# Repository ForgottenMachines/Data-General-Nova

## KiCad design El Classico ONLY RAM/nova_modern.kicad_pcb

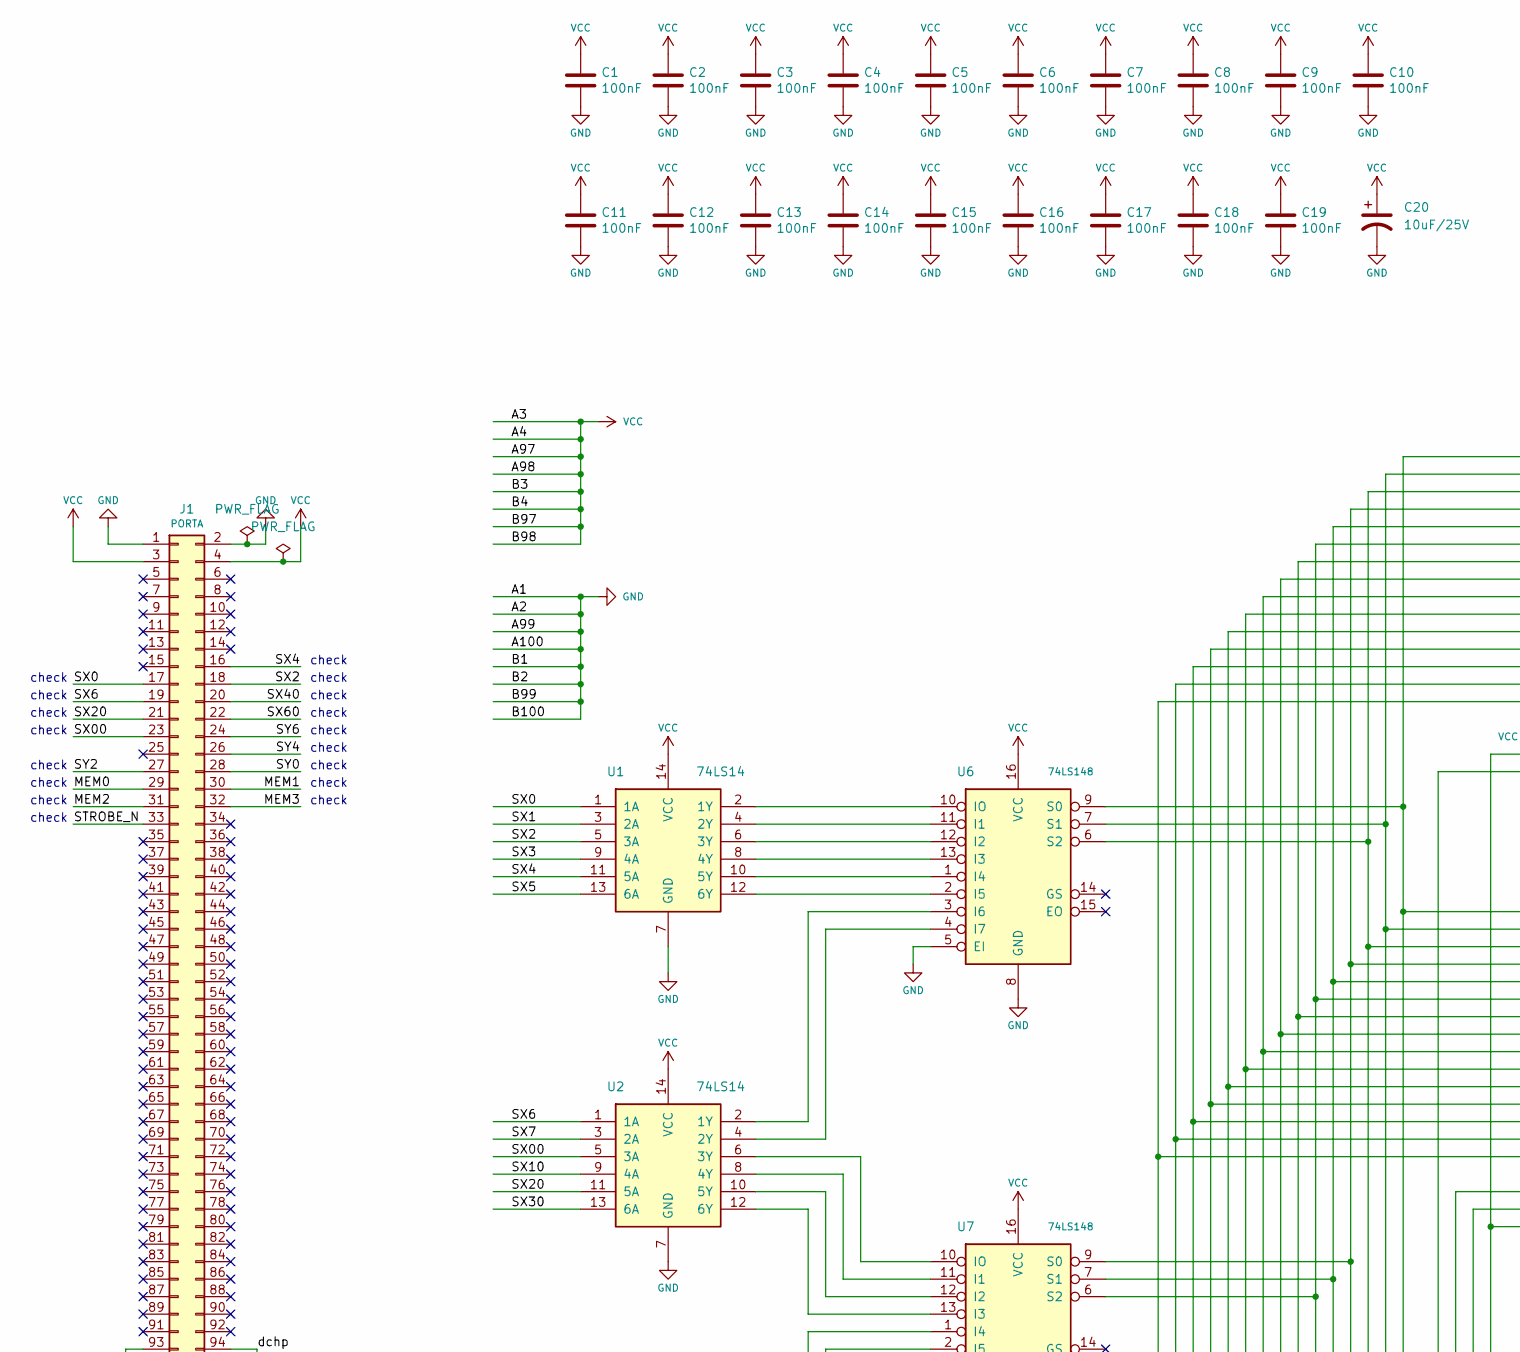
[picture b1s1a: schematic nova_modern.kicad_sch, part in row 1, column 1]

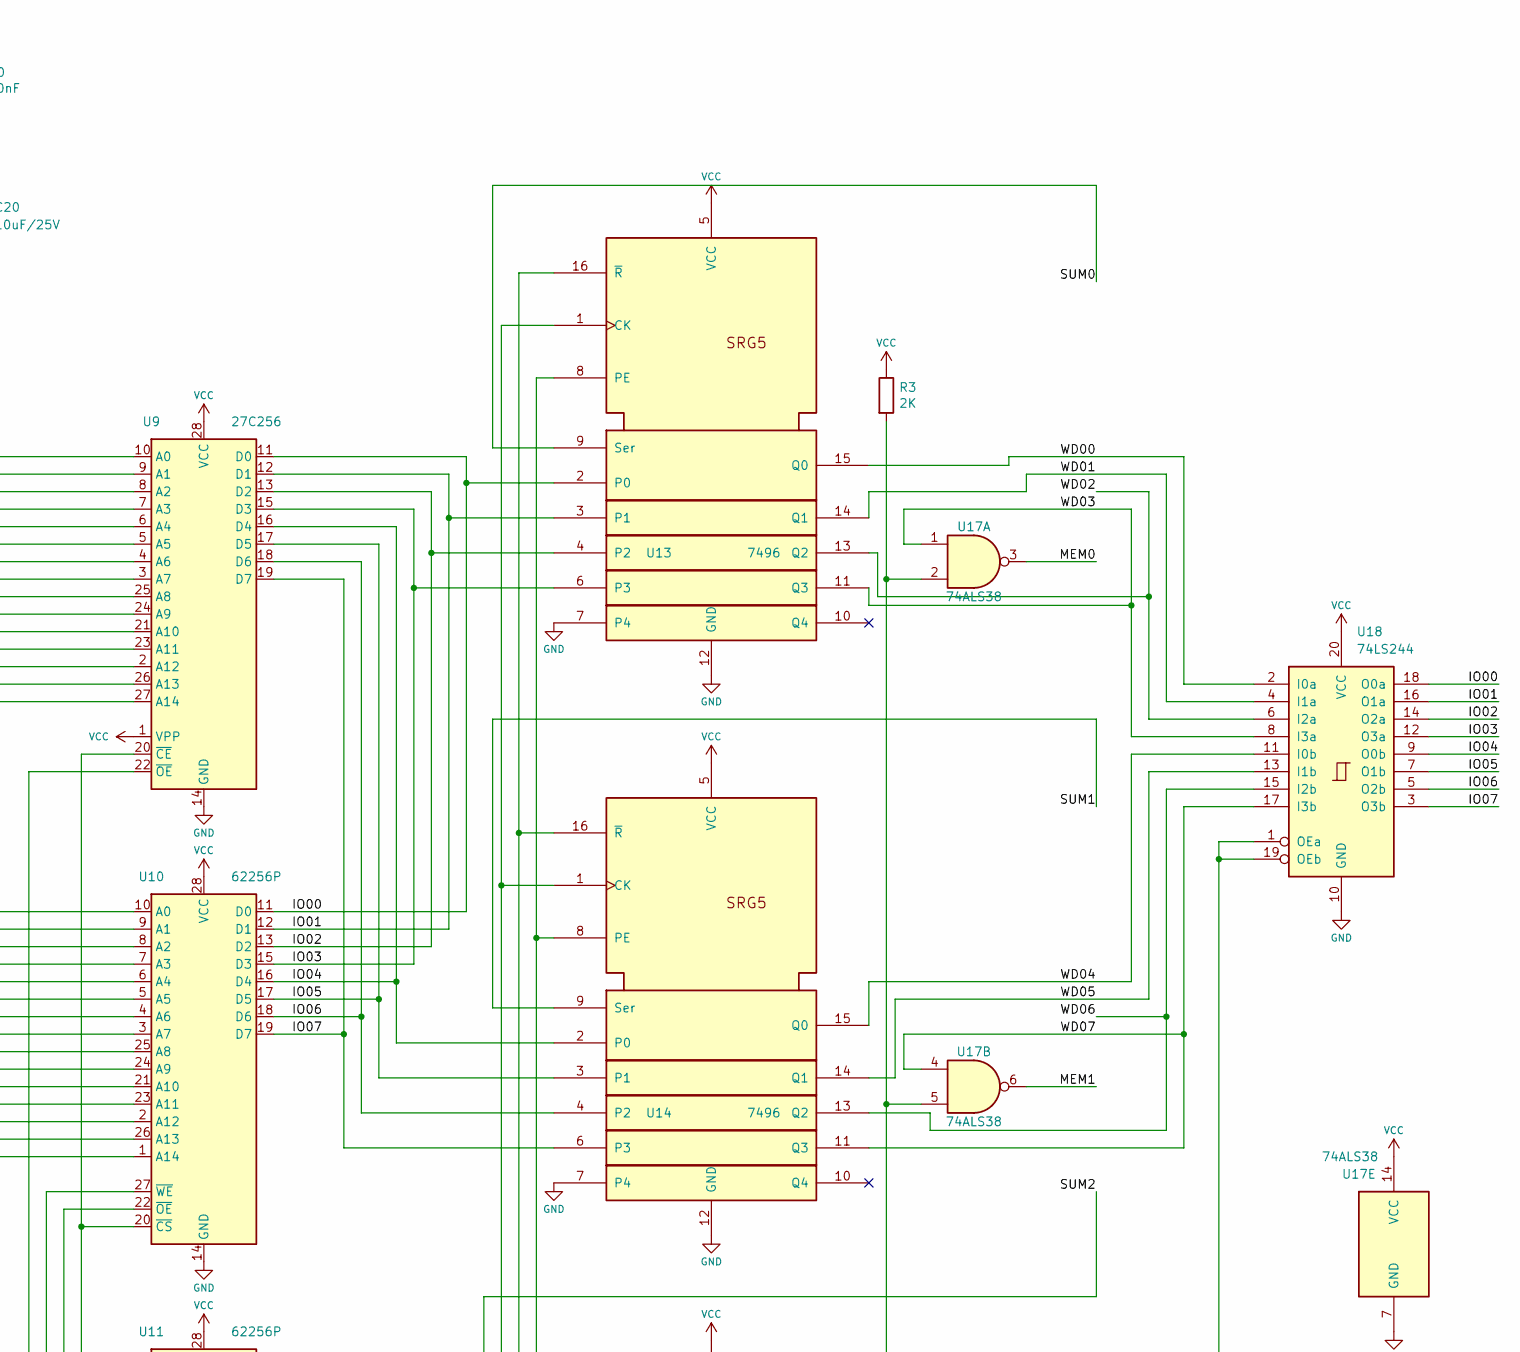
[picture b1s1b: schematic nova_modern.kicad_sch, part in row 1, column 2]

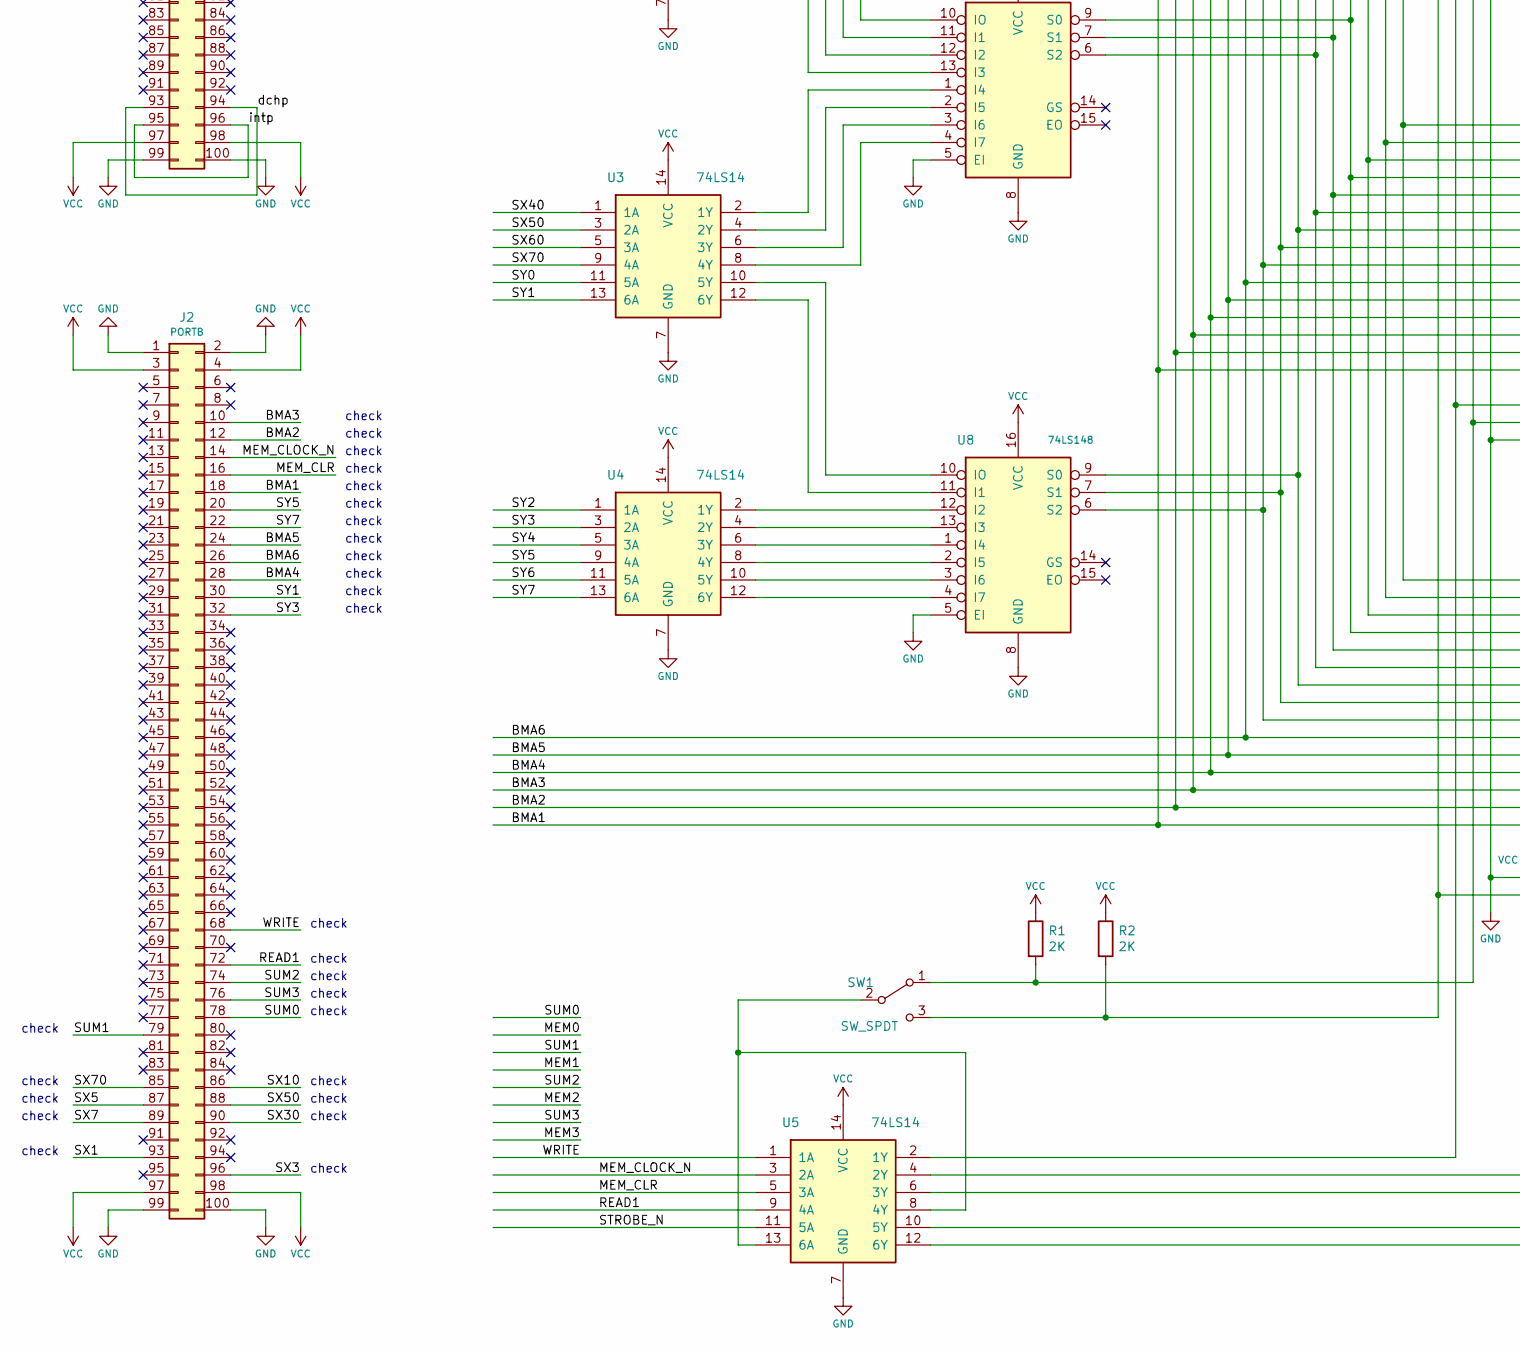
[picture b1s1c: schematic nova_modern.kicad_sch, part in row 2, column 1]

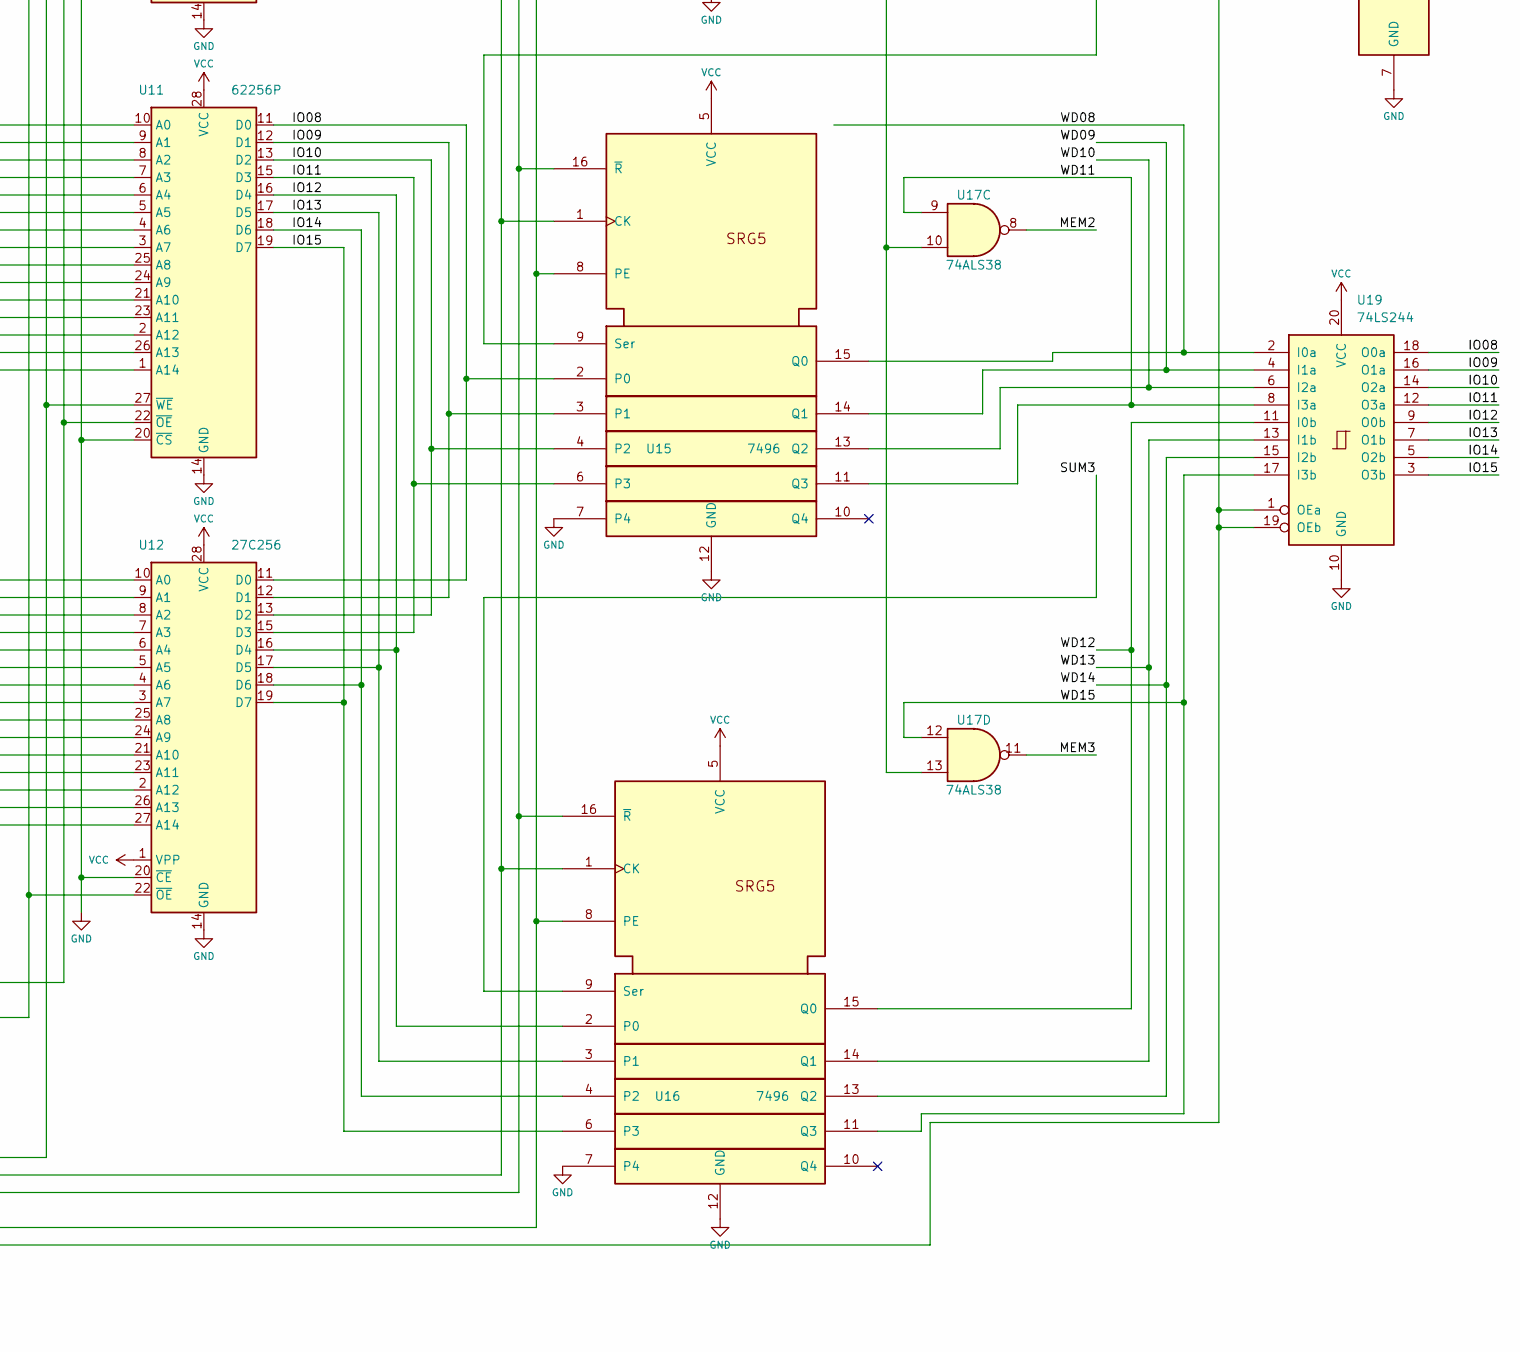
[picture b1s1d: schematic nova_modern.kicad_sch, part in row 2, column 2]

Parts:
C1, C2, C3, C4, C5, C6, C7, C8, C9, C10, C11, C12, C13, C14, C15, C16, C17, C18, C19: 100nF; C_Disc_D4.7mm_W2.5mm_P5.00mm; Part Number FA28X8R1E104KNU06; Digi-Key 445-180812-1-ND
C20: 10uF/25V; CP_Radial_D8.0mm_P3.50mm
J1: PORTA; portA_NovaMod; Part Number - - -; Digi-Key - - -
J2: PORTB; portB_NovaMod; Part Number - - -; Digi-Key - - -
R1, R2, R3: 2K; R_Axial_DIN0204_L3.6mm_D1.6mm_P7.62mm_Horizontal; Part Number CFR-25JB-52-2K; Digi-Key 2.0KQBK-ND
SW1: SW_SPDT; SW_E-Switch_EG1224_SPDT_Angled; Part Number EG1224; Digi-Key EG2585-ND
U1, U2, U3, U4, U5: 74LS14; DIP-14_W7.62mm; Part Number SN74LS14N; Digi-Key 296-1643-5-ND
U6, U7, U8: 74LS148; DIP-16_W7.62mm; Part Number SN74LS148N; Digi-Key 296-3651-5-ND
U9, U12: 27C256; DIP-28_W15.24mm; Part Number AT27C256R-70PU; Digi-Key AT27C256R-70PU-ND
U10, U11: 62256P; DIP-28_W15.24mm; Part Number AS6C62256-55PCN; Digi-Key 1450-1033-ND
U13, U14, U15, U16: 7496; DIP-16_W7.62mm; Part Number SN74LS96; Digi-Key - - -
U17: 74ALS38; DIP-14_W7.62mm; Part Number SN74ALS00AN; Digi-Key 296-1478-5-ND
U18, U19: 74LS244; DIP-20_W7.62mm

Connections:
/BMA1: J2.18, U9.27 (A14), U10.1 (A14), U11.1 (A14), U12.27 (A14)
/BMA2: J2.12, U9.26 (A13), U10.26 (A13), U11.26 (A13), U12.26 (A13)
/BMA3: J2.10, U9.2 (A12), U10.2 (A12), U11.2 (A12), U12.2 (A12)
/BMA4: J2.28, U9.23 (A11), U10.23 (A11), U11.23 (A11), U12.23 (A11)
/BMA5: J2.24, U9.21 (A10), U10.21 (A10), U11.21 (A10), U12.21 (A10)
/BMA6: J2.26, U9.24 (A9), U10.24 (A9), U11.24 (A9), U12.24 (A9)
/IO00: U9.11 (D0), U10.11 (D0), U13.2 (P0), U18.18 (O0a)
/IO01: U9.12 (D1), U10.12 (D1), U13.3 (P1), U18.16 (O1a)
/IO02: U9.13 (D2), U10.13 (D2), U13.4 (P2), U18.14 (O2a)
/IO03: U9.15 (D3), U10.15 (D3), U13.6 (P3), U18.12 (O3a)
/IO04: U9.16 (D4), U10.16 (D4), U14.2 (P0), U18.9 (O0b)
/IO05: U9.17 (D5), U10.17 (D5), U14.3 (P1), U18.7 (O1b)
/IO06: U9.18 (D6), U10.18 (D6), U14.4 (P2), U18.5 (O2b)
/IO07: U9.19 (D7), U10.19 (D7), U14.6 (P3), U18.3 (O3b)
/IO08: U11.11 (D0), U12.11 (D0), U15.2 (P0), U19.18 (O0a)
/IO09: U11.12 (D1), U12.12 (D1), U15.3 (P1), U19.16 (O1a)
/IO10: U11.13 (D2), U12.13 (D2), U15.4 (P2), U19.14 (O2a)
/IO11: U11.15 (D3), U12.15 (D3), U15.6 (P3), U19.12 (O3a)
/IO12: U11.16 (D4), U12.16 (D4), U16.2 (P0), U19.9 (O0b)
/IO13: U11.17 (D5), U12.17 (D5), U16.3 (P1), U19.7 (O1b)
/IO14: U11.18 (D6), U12.18 (D6), U16.4 (P2), U19.5 (O2b)
/IO15: U11.19 (D7), U12.19 (D7), U16.6 (P3), U19.3 (O3b)
/MEM0: J1.29, U17.3
/MEM1: J1.30, U17.6
/MEM2: J1.31, U17.8
/MEM3: J1.32, U17.11
/MEM_CLOCK_N: J2.14, U5.3 (2A)
/MEM_CLR: J2.16, U5.5 (3A)
/READ1: J2.72, U5.9 (4A)
/STROBE_N: J1.33, U5.11 (5A)
/SUM0: J2.78, U13.9 (Ser)
/SUM1: J2.79, U14.9 (Ser)
/SUM2: J2.74, U15.9 (Ser)
/SUM3: J2.76, U16.9 (Ser)
/SX0: J1.17, U1.1 (1A)
/SX00: J1.23, U2.5 (3A)
/SX1: J2.93, U1.3 (2A)
/SX2: J1.18, U1.5 (3A)
/SX3: J2.96, U1.9 (4A)
/SX4: J1.16, U1.11 (5A)
/SX5: J2.87, U1.13 (6A)
/SX6: J1.19, U2.1 (1A)
/SX7: J2.89, U2.3 (2A)
/SX10: J2.86, U2.9 (4A)
/SX20: J1.21, U2.11 (5A)
/SX30: J2.90, U2.13 (6A)
/SX40: J1.20, U3.1 (1A)
/SX50: J2.88, U3.3 (2A)
/SX60: J1.22, U3.5 (3A)
/SX70: J2.85, U3.9 (4A)
/SY0: J1.28, U3.11 (5A)
/SY1: J2.30, U3.13 (6A)
/SY2: J1.27, U4.1 (1A)
/SY3: J2.32, U4.3 (2A)
/SY4: J1.26, U4.5 (3A)
/SY5: J2.20, U4.9 (4A)
/SY6: J1.24, U4.11 (5A)
/SY7: J2.22, U4.13 (6A)
/WD00: U13.15 (Q0), U18.2 (I0a)
/WD01: U13.14 (Q1), U18.4 (I1a)
/WD02: U13.13 (Q2), U18.6 (I2a)
/WD03: U13.11 (Q3), U17.1, U18.8 (I3a)
/WD04: U14.15 (Q0), U18.11 (I0b)
/WD05: U14.14 (Q1), U18.13 (I1b)
/WD06: U14.13 (Q2), U18.15 (I2b)
/WD07: U14.11 (Q3), U17.4, U18.17 (I3b)
/WD08: U15.15 (Q0), U19.2 (I0a)
/WD09: U15.14 (Q1), U19.4 (I1a)
/WD10: U15.13 (Q2), U19.6 (I2a)
/WD11: U15.11 (Q3), U17.9, U19.8 (I3a)
/WD12: U16.15 (Q0), U19.11 (I0b)
/WD13: U16.14 (Q1), U19.13 (I1b)
/WD14: U16.13 (Q2), U19.15 (I2b)
/WD15: U16.11 (Q3), U17.12, U19.17 (I3b)
/WRITE: J2.68, U5.1 (1A)
/dchp: J1.93, J1.94
/intp: J1.95, J1.96
GND: C1.2, C2.2, C3.2, C4.2, C5.2, C6.2, C7.2, C8.2, C9.2, C10.2, C11.2, C12.2, C13.2, C14.2, C15.2, C16.2, C17.2, C18.2, C19.2, C20.2, J1.1, J1.2, J1.99, J1.100, J2.1, J2.2, J2.99, J2.100, U1.7 (GND), U2.7 (GND), U3.7 (GND), U4.7 (GND), U5.7 (GND), U6.5 (EI), U6.8 (GND), U7.5 (EI), U7.8 (GND), U8.5 (EI), U8.8 (GND), U9.14 (GND), U9.20 (~CE), U10.14 (GND), U10.20 (~CS), U11.14 (GND), U11.20 (~CS), U12.14 (GND), U12.20 (~CE), U13.7 (P4), U13.12 (GND), U14.7 (P4), U14.12 (GND), U15.7 (P4), U15.12 (GND), U16.7 (P4), U16.12 (GND), U17.7 (GND), U18.10 (GND), U19.10 (GND)
unnamed: R3.2, U17.2, U17.5, U17.10, U17.13
unnamed: R1.2, SW1.1 (A), U10.22 (~OE), U11.22 (~OE)
unnamed: SW1.2 (B), U5.8 (4Y), U5.13 (6A)
unnamed: R2.2, SW1.3 (C), U9.22 (~OE), U12.22 (~OE)
unnamed: U1.2 (1Y), U6.10 (IO)
unnamed: U1.4 (2Y), U6.11 (I1)
unnamed: U1.6 (3Y), U6.12 (I2)
unnamed: U1.8 (4Y), U6.13 (I3)
unnamed: U1.10 (5Y), U6.1 (I4)
unnamed: U1.12 (6Y), U6.2 (I5)
unnamed: U2.2 (1Y), U6.3 (I6)
unnamed: U2.4 (2Y), U6.4 (I7)
unnamed: U2.6 (3Y), U7.10 (IO)
unnamed: U2.8 (4Y), U7.11 (I1)
unnamed: U2.10 (5Y), U7.12 (I2)
unnamed: U2.12 (6Y), U7.13 (I3)
unnamed: U3.2 (1Y), U7.1 (I4)
unnamed: U3.4 (2Y), U7.2 (I5)
unnamed: U3.6 (3Y), U7.3 (I6)
unnamed: U3.8 (4Y), U7.4 (I7)
unnamed: U3.10 (5Y), U8.10 (IO)
unnamed: U3.12 (6Y), U8.11 (I1)
unnamed: U4.2 (1Y), U8.12 (I2)
unnamed: U4.4 (2Y), U8.13 (I3)
unnamed: U4.6 (3Y), U8.1 (I4)
unnamed: U4.8 (4Y), U8.2 (I5)
unnamed: U4.10 (5Y), U8.3 (I6)
unnamed: U4.12 (6Y), U8.4 (I7)
unnamed: U6.9 (S0), U9.10 (A0), U10.10 (A0), U11.10 (A0), U12.10 (A0)
unnamed: U6.7 (S1), U9.9 (A1), U10.9 (A1), U11.9 (A1), U12.9 (A1)
unnamed: U6.6 (S2), U9.8 (A2), U10.8 (A2), U11.8 (A2), U12.8 (A2)
unnamed: U7.9 (S0), U9.7 (A3), U10.7 (A3), U11.7 (A3), U12.7 (A3)
unnamed: U7.7 (S1), U9.6 (A4), U10.6 (A4), U11.6 (A4), U12.6 (A4)
unnamed: U7.6 (S2), U9.5 (A5), U10.5 (A5), U11.5 (A5), U12.5 (A5)
unnamed: U8.9 (S0), U9.4 (A6), U10.4 (A6), U11.4 (A6), U12.4 (A6)
unnamed: U8.7 (S1), U9.3 (A7), U10.3 (A7), U11.3 (A7), U12.3 (A7)
unnamed: U8.6 (S2), U9.25 (A8), U10.25 (A8), U11.25 (A8), U12.25 (A8)
unnamed: U5.2 (1Y), U10.27 (~WE), U11.27 (~WE)
unnamed: U5.4 (2Y), U13.1 (CK), U14.1 (CK), U15.1 (CK), U16.1 (CK)
unnamed: U5.10 (5Y), U13.8 (PE), U14.8 (PE), U15.8 (PE), U16.8 (PE)
unnamed: U5.6 (3Y), U13.16 (~R), U14.16 (~R), U15.16 (~R), U16.16 (~R)
unnamed: U5.12 (6Y), U18.1 (OEa), U18.19 (OEb), U19.1 (OEa), U19.19 (OEb)
VCC: C1.1, C2.1, C3.1, C4.1, C5.1, C6.1, C7.1, C8.1, C9.1, C10.1, C11.1, C12.1, C13.1, C14.1, C15.1, C16.1, C17.1, C18.1, C19.1, C20.1, J1.3, J1.4, J1.97 (Pin_69), J1.98, J2.3, J2.4, J2.97 (Pin_69), J2.98, R1.1, R2.1, R3.1, U1.14 (VCC), U2.14 (VCC), U3.14 (VCC), U4.14 (VCC), U5.14 (VCC), U6.16 (VCC), U7.16 (VCC), U8.16 (VCC), U9.1 (VPP), U9.28 (VCC), U10.28 (VCC), U11.28 (VCC), U12.1 (VPP), U12.28 (VCC), U13.5 (VCC), U14.5 (VCC), U15.5 (VCC), U16.5 (VCC), U17.14 (VCC), U18.20 (VCC), U19.20 (VCC)

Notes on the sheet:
check

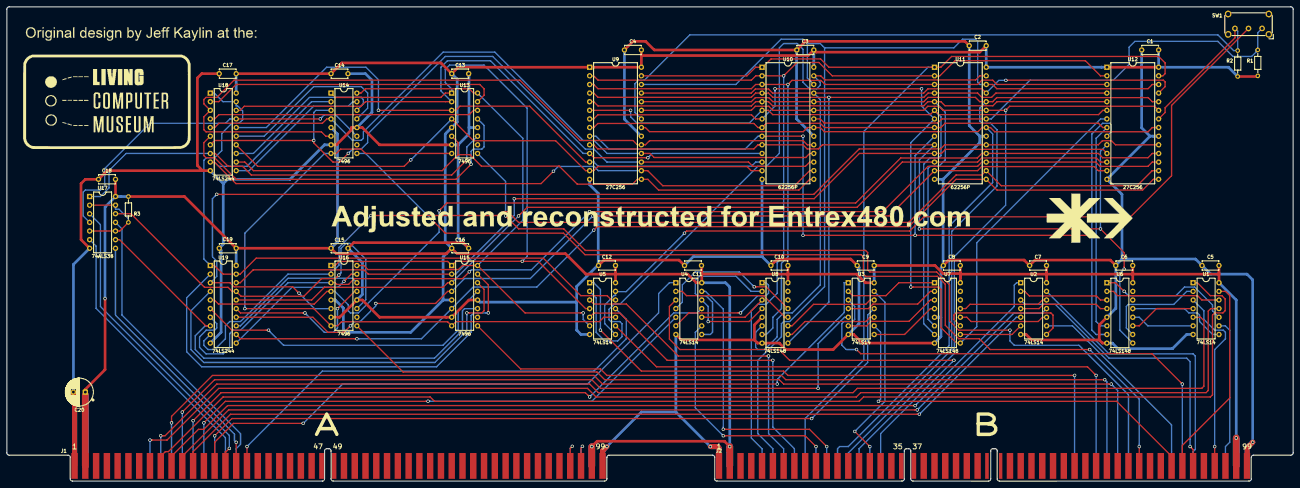
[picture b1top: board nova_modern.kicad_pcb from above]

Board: 2 copper layers, 379.0 x 139.7 mm, 45 parts (0 on the bottom side), 121 nets.

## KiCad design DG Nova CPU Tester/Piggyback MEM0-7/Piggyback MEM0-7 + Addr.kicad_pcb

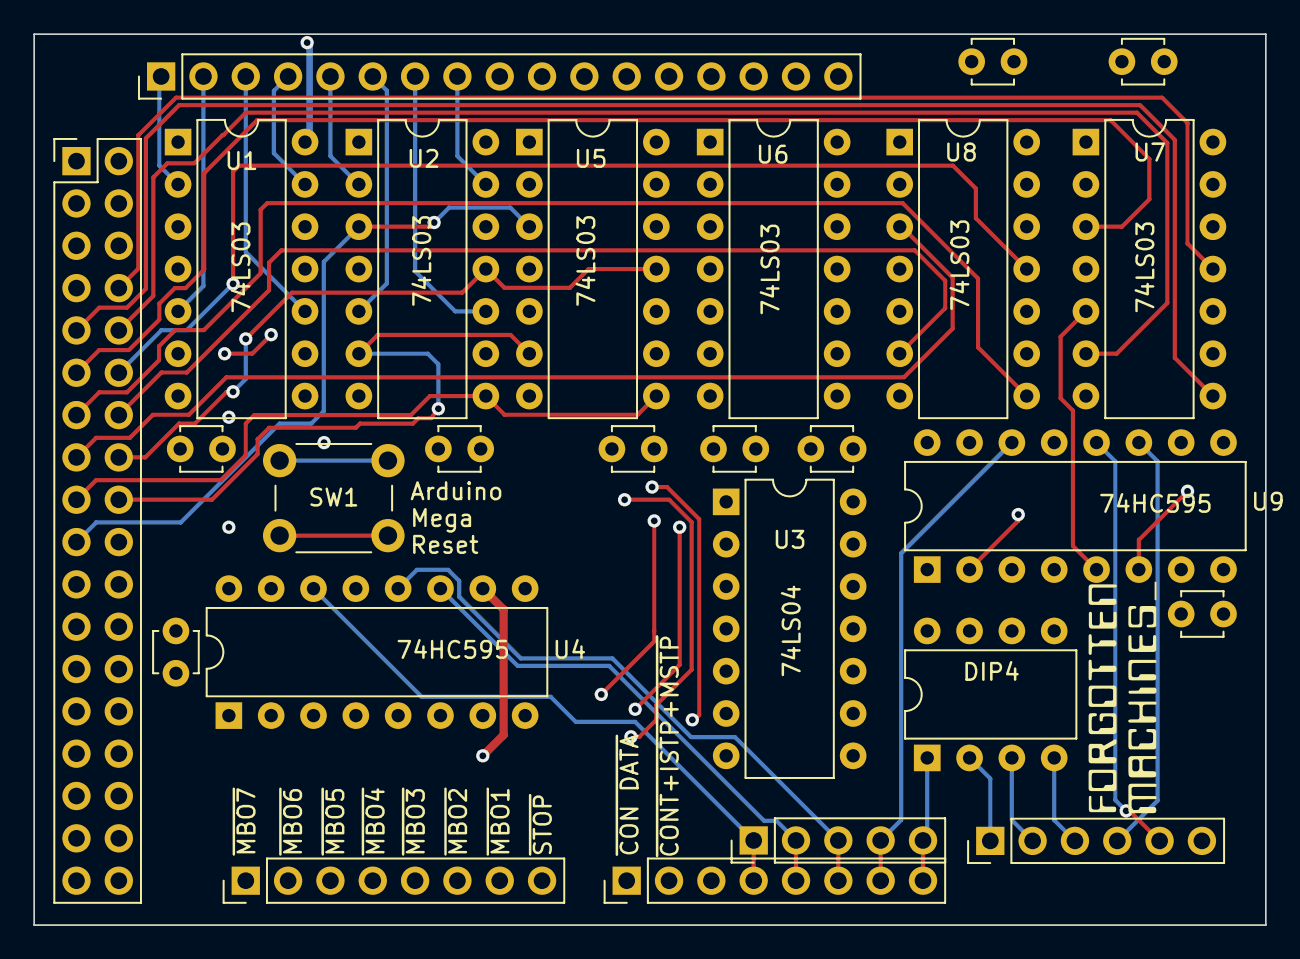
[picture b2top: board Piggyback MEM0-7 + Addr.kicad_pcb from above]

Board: 4 copper layers, 73.9 x 53.5 mm, 26 parts (0 on the bottom side), 56 nets.

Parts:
C1, C2, C3, C4, C5, C6, C7, C8, C9: CAP_Disc_Common_-_Entrex_Trapezoid; Disc Capacitor Entrex Trapezoid .10
J1: Conn_02x18_Odd_Even; PinHeader_2x18_P2.54mm_Vertical
J2: Arduino Digital Pins; PinHeader_1x05_P2.54mm_Vertical
J3: Conn_01x17; PinHeader_1x17_P2.54mm_Vertical
J4: Arduino Digital Pins; PinHeader_1x06_P2.54mm_Vertical
J5, J6: Conn_01x08; PinHeader_1x08_P2.54mm_Vertical
SW1: Arduino Mega Reset; SW_PUSH_6mm
SW2: SW_DIP_x04; DIP-8_W7.62mm
U1, U2, U5, U6, U7, U8: 74LS03; DIP-14_W7.62mm
U3: 74LS04; DIP-14_W7.62mm
U4, U9: 74HC595; DIP-16_W7.62mm

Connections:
+5V: C1.1, C2.1, C3.1, C4.1, C5.1, C6.1, C7.1, C8.1, C9.1, J1.35, J1.36, U1.14 (VCC), U2.14 (VCC), U3.14 (VCC), U4.10 (~SRCLR), U4.16 (VCC), U5.14 (VCC), U6.14 (VCC), U7.14 (VCC), U8.14 (VCC), U9.10 (~SRCLR), U9.16 (VCC)
A08: J3.8, U2.13
A09: J3.7, U2.10
A10: J3.6, U2.5
A11: J3.5, U2.2
A12: J3.4, U1.13
A13: J3.3, U1.10
A14: J3.2, U1.5
A15: J3.1, U1.2
Addr00: U4.15 (QA), U6.2
Addr01: U4.1 (QB), U6.5
Addr02: U4.2 (QC), U6.10
Addr03: U4.3 (QD), U6.13
Addr04: U4.4 (QE), U5.2
Addr05: U4.5 (QF), U5.5
Addr06: U4.6 (QG), U5.10
Addr07: U4.7 (QH), U5.13
Addr08: U8.2, U9.15 (QA)
Addr09: U8.5, U9.1 (QB)
Addr10: U8.10, U9.2 (QC)
Addr11: U8.13, U9.3 (QD)
Addr12: U7.2, U9.4 (QE)
Addr13: U7.5, U9.5 (QF)
Addr14: U7.10, U9.6 (QG)
Addr15: U7.13, U9.7 (QH)
CON DATA: U3.4, U5.1, U5.4, U5.9, U5.12, U6.1, U6.4, U6.9, U6.12, U7.1, U7.4, U7.9, U7.12, U8.1, U8.4, U8.9, U8.12
CON INST: U1.1, U1.4, U1.9, U1.12, U2.1, U2.4, U2.9, U2.12, U3.2
ClockPin1: J2.2, J6.5, U4.11 (SRCLK)
ClockPin2: J4.4, U9.11 (SRCLK)
DIP1: J4.3, SW2.4
DIP2: J4.2, SW2.3
DIP3: J4.1, SW2.2
DIP4: J2.5, J6.8, SW2.1
DataPin1: J2.1, J6.4, U4.14 (SER)
DataPin2: J2.4, J6.7, U9.14 (SER)
GND: C1.2, C2.2, C3.2, C4.2, C5.2, C6.2, C7.2, C8.2, C9.2, J1.1, J1.2, SW1.2, SW2.5, SW2.6, SW2.7, SW2.8, U1.7 (GND), U2.7 (GND), U3.7 (GND), U4.8 (GND), U4.13 (~OE), U5.7 (GND), U6.7 (GND), U7.7 (GND), U8.7 (GND), U9.8 (GND), U9.13 (~OE)
LatchPin1: J2.3, J6.6, U4.12 (RCLK)
LatchPin2: J4.5, U9.12 (RCLK)
~CON DATA: J6.1, U3.3
~CON INST: J3.13, U3.1
~MEM0: J1.23, U1.3, U6.3
~MEM1: J1.22, U1.6, U6.6
~MEM2: J1.21, U1.8, U6.8
~MEM3: J1.20, U1.11, U6.11
~MEM4: J1.19, U2.3, U5.3
~MEM5: J1.18, U2.6, U5.6
~MEM6: J1.17, U2.8, U5.8
~MEM7: J1.16, U2.11, U5.11
~MEM8: J1.15, U8.3
~MEM9: J1.14, U8.6
~MEM10: J1.13, U8.8
~MEM11: J1.12, U8.11
~MEM12: J1.11, U7.3
~MEM13: J1.10, U7.6
~MEM14: J1.9, U7.8
~MEM15: J1.8, U7.11

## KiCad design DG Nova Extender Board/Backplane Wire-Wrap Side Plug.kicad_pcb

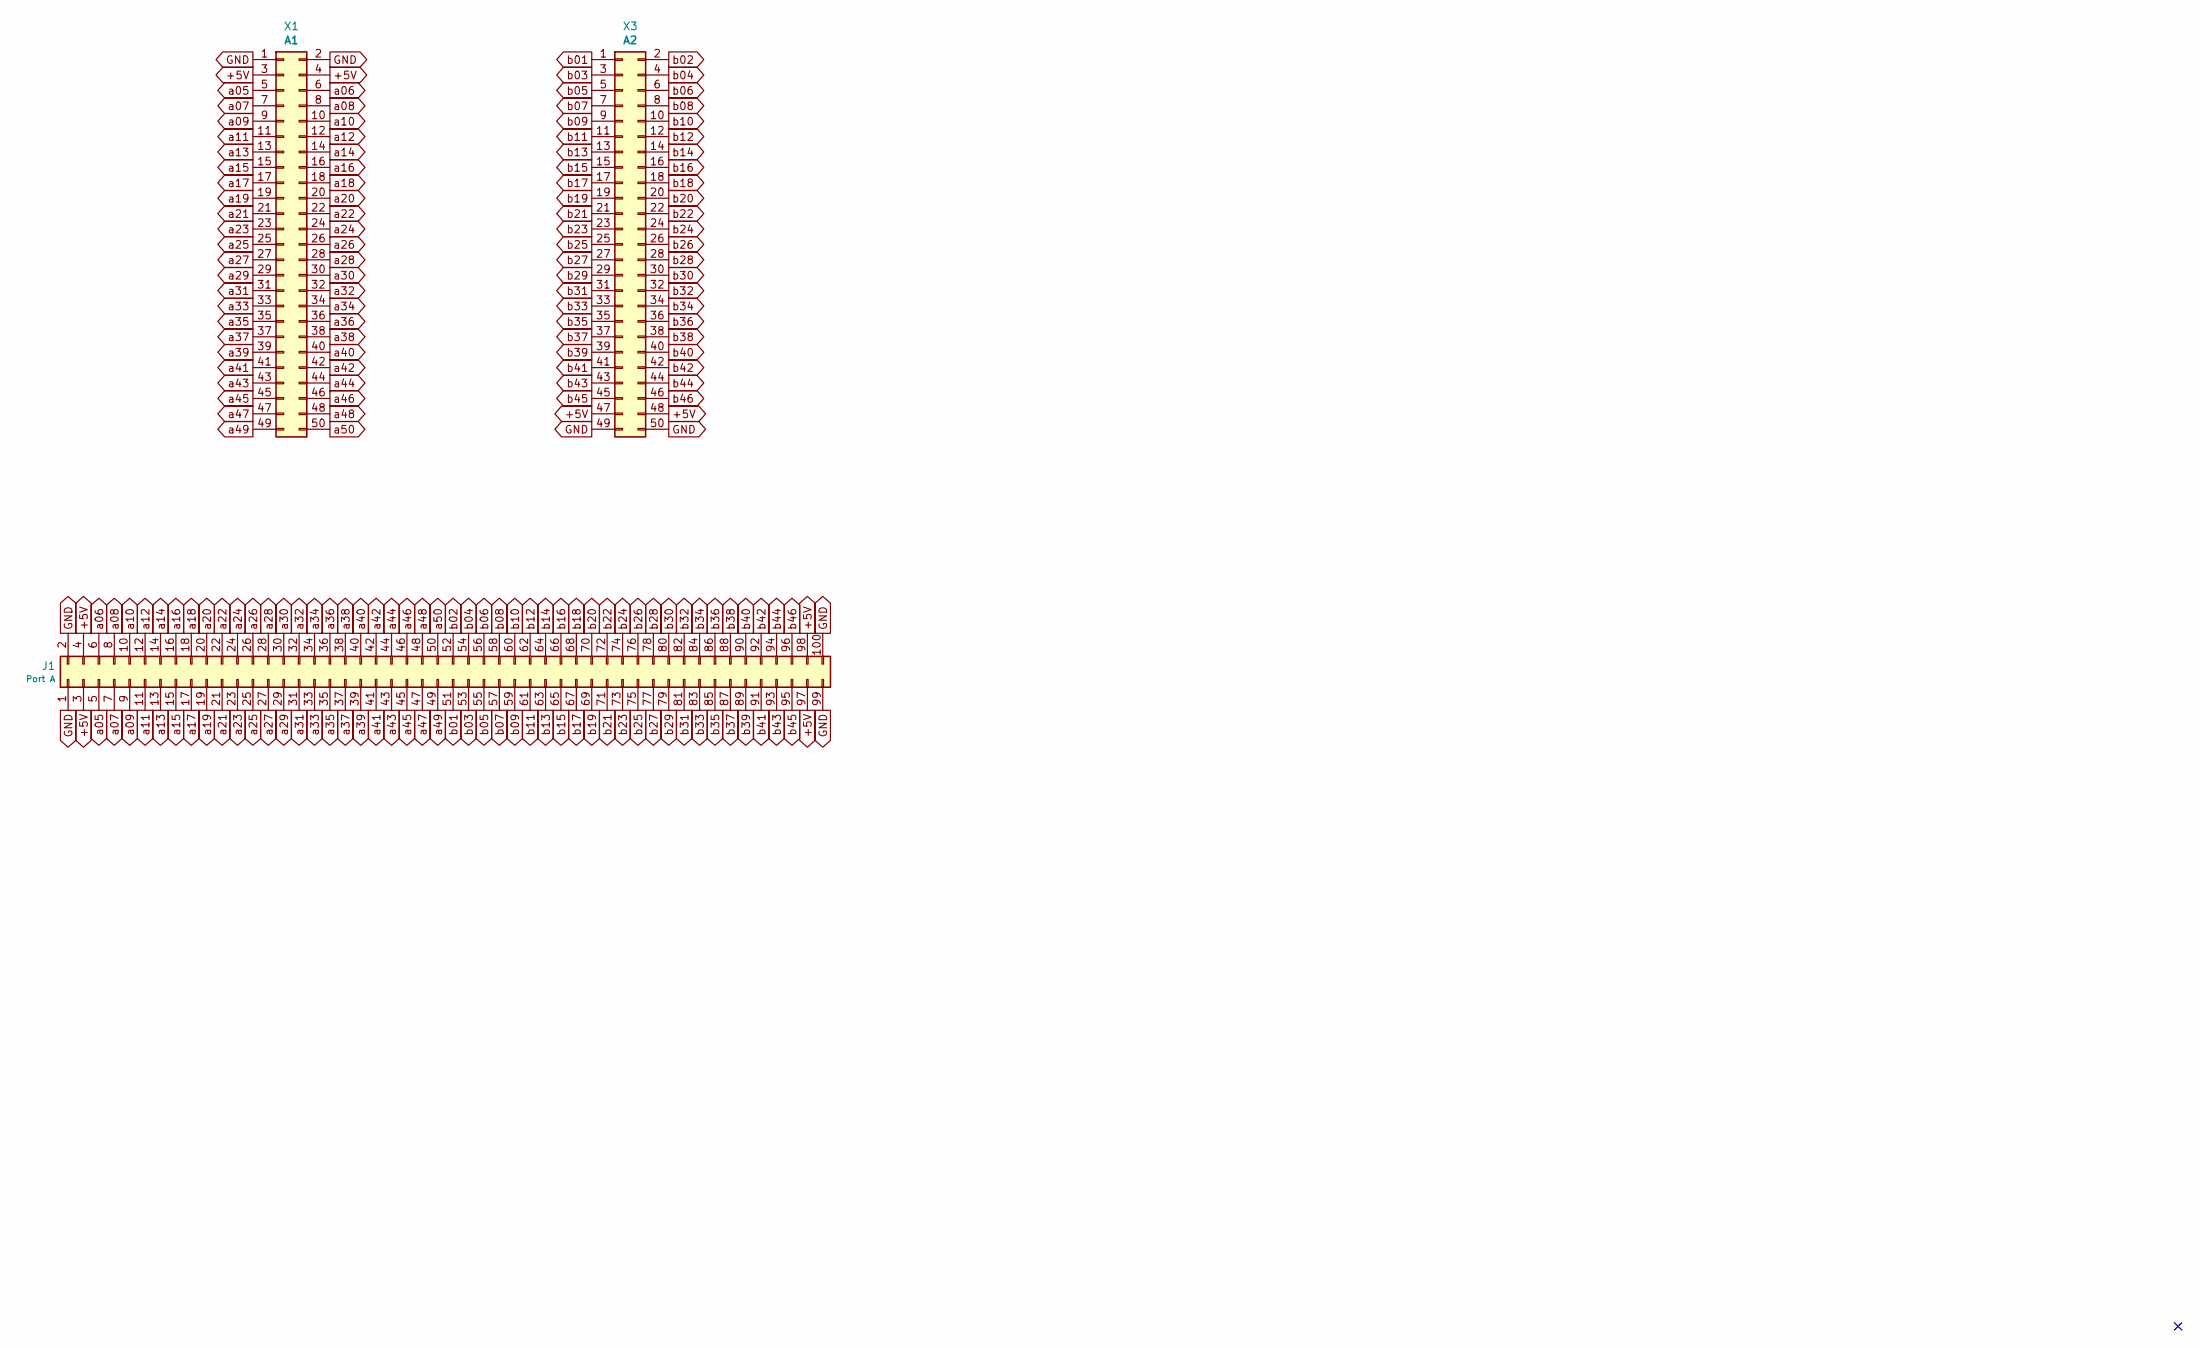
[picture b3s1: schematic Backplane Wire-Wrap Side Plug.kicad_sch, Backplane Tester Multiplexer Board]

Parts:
J1: Port A; DG NOVA Backplane Connector - Frontside
X1: A1; IDC-Header_2x25_P2.54mm - Backside; Part-Number SBH11-PBPC-D25-ST-BK; Digi-Key S9176-ND
X3: A2; IDC-Header_2x25_P2.54mm - Backside; Part-Number SBH11-PBPC-D25-ST-BK; Digi-Key S9176-ND

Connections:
+5V: J1.3, J1.4, J1.97 (Pin_69), J1.98, X1.3, X1.4, X3.47, X3.48
GND: J1.1, J1.2, J1.99, J1.100, X1.1, X1.2, X3.49, X3.50
a05: J1.5, X1.5
a06: J1.6, X1.6
a07: J1.7, X1.7
a08: J1.8, X1.8
a09: J1.9, X1.9
a10: J1.10, X1.10
a11: J1.11, X1.11
a12: J1.12, X1.12
a13: J1.13, X1.13
a14: J1.14, X1.14
a15: J1.15, X1.15
a16: J1.16, X1.16
a17: J1.17, X1.17
a18: J1.18, X1.18
a19: J1.19, X1.19
a20: J1.20, X1.20
a21: J1.21, X1.21
a22: J1.22, X1.22
a23: J1.23, X1.23
a24: J1.24, X1.24
a25: J1.25, X1.25
a26: J1.26, X1.26
a27: J1.27, X1.27
a28: J1.28, X1.28
a29: J1.29, X1.29
a30: J1.30, X1.30
a31: J1.31, X1.31
a32: J1.32, X1.32
a33: J1.33, X1.33
a34: J1.34, X1.34
a35: J1.35, X1.35
a36: J1.36, X1.36
a37: J1.37, X1.37
a38: J1.38, X1.38
a39: J1.39, X1.39
a40: J1.40, X1.40
a41: J1.41, X1.41
a42: J1.42, X1.42
a43: J1.43, X1.43
a44: J1.44, X1.44
a45: J1.45, X1.45
a46: J1.46, X1.46
a47: J1.47, X1.47
a48: J1.48, X1.48
a49: J1.49, X1.49
a50: J1.50, X1.50
b01: J1.51, X3.1
b02: J1.52, X3.2
b03: J1.53, X3.3
b04: J1.54, X3.4
b05: J1.55, X3.5
b06: J1.56, X3.6
b07: J1.57, X3.7
b08: J1.58, X3.8
b09: J1.59, X3.9
b10: J1.60, X3.10
b11: J1.61, X3.11
b12: J1.62, X3.12
b13: J1.63, X3.13
b14: J1.64, X3.14
b15: J1.65, X3.15
b16: J1.66, X3.16
b17: J1.67, X3.17
b18: J1.68, X3.18
b19: J1.69, X3.19
b20: J1.70, X3.20
b21: J1.71, X3.21
b22: J1.72, X3.22
b23: J1.73, X3.23
b24: J1.74, X3.24
b25: J1.75, X3.25
b26: J1.76, X3.26
b27: J1.77, X3.27
b28: J1.78, X3.28
b29: J1.79, X3.29
b30: J1.80, X3.30
b31: J1.81, X3.31
b32: J1.82, X3.32
b33: J1.83, X3.33
b34: J1.84, X3.34
b35: J1.85, X3.35
b36: J1.86, X3.36
b37: J1.87, X3.37
b38: J1.88, X3.38
b39: J1.89, X3.39
b40: J1.90, X3.40
b41: J1.91, X3.41
b42: J1.92, X3.42
b43: J1.93, X3.43
b44: J1.94, X3.44
b45: J1.95, X3.45
b46: J1.96, X3.46

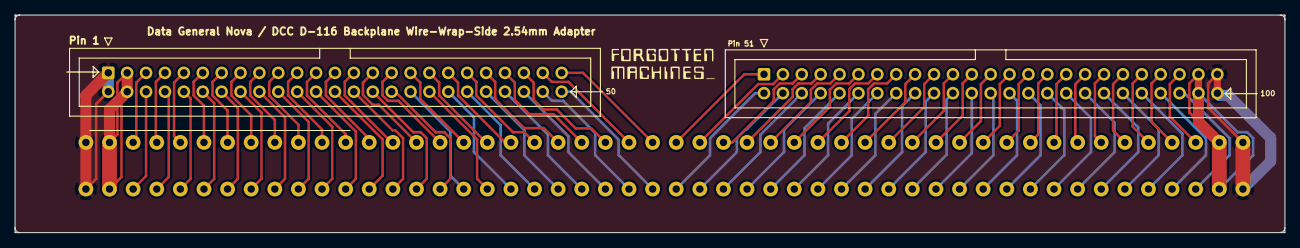
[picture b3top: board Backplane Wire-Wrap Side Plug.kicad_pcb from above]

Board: 2 copper layers, 170.8 x 29.3 mm, 3 parts (1 on the bottom side), 94 nets.
